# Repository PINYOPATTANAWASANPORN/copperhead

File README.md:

<p align="center">
  
</p>

<p align="center">

</p>

**Cursor for circuit boards.** An AI agent that designs, documents, and validates real PCBs from a prompt, working directly on existing KiCad repositories.

> **Status: early.** Phase 1 is implemented and the CLI runs. The [technical specification](openspec/specs/SPEC.md) is the source of truth; expect the surface to move before 1.0.

Full documentation lives at [docs.copperhead.sh](https://docs.copperhead.sh).

## What it is

An AI product-development agent for hardware: from a product brief to manufacturable files, firmware, and a build plan.

- **`copperhead create`**: full pipeline from a natural-language brief: spec, architecture, part selection, schematic, first-draft layout, then gerbers, firmware scaffold, and dev plan.
- **`copperhead do "<change>"`**: operates on an existing KiCad repo the way a coding agent operates on a codebase.

It reads and edits real `.kicad_sch` / `.kicad_pcb` files (s-expression text), maintains markdown design docs as memory, propagates every change across all artifacts that reference it, and verifies its own work by running `kicad-cli` ERC/DRC until the checks pass.

## Install

> [!TIP]
> **Most users should not install copperhead by hand.** If you are working inside an AI coding assistant (like Claude Code, Cursor, or Codex), you can install and configure copperhead automatically for your repository by pasting this single line:
> ```text
> Install copperhead for this repo using https://raw.githubusercontent.com/copperheadhq/copperhead/main/agent-install-prompt.md
> ```

If you prefer to install manually:

```bash
npm install -g copperhead   # or: npx copperhead check
```

### Bootstrap script (macOS and Linux)

Prefer a one-command setup? [`install.sh`](install.sh) checks the prerequisites below, installs copperhead (globally via npm, or built from source when run inside a checkout), and verifies the result with `copperhead doctor`:

```bash
./install.sh                # interactive: asks before installing anything
./install.sh --yes          # assume yes to the install prompts
./install.sh --check-only   # report what is missing, install nothing
```

The script is conservative by design: it never runs `sudo` and never edits shell config; whenever it cannot act safely on its own it prints the exact command for you to run instead. Rerunning is safe: on a ready machine it installs nothing and exits 0.

### Requirements

- Node.js ≥ 20
- [KiCad](https://www.kicad.org/) ≥ 8 with `kicad-cli` on PATH (on Windows and macOS, copperhead also searches standard installation directories automatically; override with `COPPERHEAD_KICAD_CLI`)
- One model backend: a locally installed, ChatGPT-authenticated [Codex CLI](https://learn.chatgpt.com/docs/codex/cli), a logged-in [Cursor Agent CLI](#saved-login-cursor-agent) (`agent login`), logged-in Claude Code (see [Saved login](#saved-login-claude-code)), or `ANTHROPIC_API_KEY`/`OPENAI_API_KEY` in the environment. `check` never calls an LLM.

## Quick start

In an existing KiCad repository:

```bash
export ANTHROPIC_API_KEY=...   # or OPENAI_API_KEY; optional: with no key, `copperhead` offers a model picker
copperhead init                # scaffold docs/ from the schematic; idempotent
copperhead                     # interactive agent shell (Claude Code–style REPL)
copperhead demo --tour          # what the agent does (no LLM)
copperhead demo --model cursor # full USB-C breakout create pipeline
# or one-shot:
copperhead do "add reverse-polarity protection on VIN"
copperhead check               # ERC + DRC + doc drift; no LLM, CI-safe
```

Starting from nothing instead? Write a product brief and run `copperhead create --brief brief.md`. The [examples/](examples/) directory has ready-made briefs sorted by difficulty, plus a note on which one is designed to fail.

### Use your existing Codex login

No model API key is needed when Codex CLI is already authenticated:

```bash
npm install -g @openai/codex-sdk   # optional adapter, loaded only for --model codex
codex login status
copperhead do "rename net KEY_DAH to KEY_DASH" --model codex
```

Plain `codex` follows your Codex model configuration. Use `codex:<model-id>` for an explicit model. If the executable is not on `PATH`, set `COPPERHEAD_CODEX_PATH=/absolute/path/to/codex`.
The optional SDK also installs a compatible launcher; for a global install, use
`COPPERHEAD_CODEX_PATH="$(npm root -g)/@openai/codex/bin/codex.js"` as a fallback.

Codex's read-only sandbox prevents native writes but does not confine native reads. Copperhead instructs Codex not to use its own filesystem tools, but the CLI can technically read files such as `.env`. Codex also keeps session logs under `~/.codex/sessions/`; those files are outside Copperhead's transcript-redaction boundary and should be protected according to your local data-retention policy.

## How it works

It's a loop, and it looks a lot like pair-programming, except the codebase is a circuit board.

1. **Start from the docs.** Every decision lives in the design docs, so the agent reads those first and knows the whole design, not just the part in front of it.
2. **Talk through the change.** Describe what you want ("add an external key jack", "cut the sleep current"). The agent proposes the parts and circuit; you push back until the reasoning holds up.
3. **Edit the real files.** The agent writes changes straight into the KiCad schematic and the design docs, using the same part names and net names everywhere so nothing drifts.
4. **Propagate.** Change one value, like a charge current or a pin, and it carries across every doc and schematic that references it. The boring, easy-to-get-wrong step is the one the agent is best at.
5. **Check the work.** The agent runs ERC/DRC, reads the errors back, and fixes them. Nothing is "done" until the tools agree.
6. **Write down why.** Every real decision gets a one-line reason next to it, so the next change doesn't quietly undo it.

Two invariants make this trustworthy:

1. **Nothing starts without a spec.** The agent cannot touch a KiCad file until a validated change proposal exists; the edit tools are structurally unavailable until it does. Every edit is traceable to a documented intent.
2. **Nothing is "done" until the tools agree.** Every file mutation is followed by an ERC/DRC run before the agent reports success.

Spec-gated in, verification-gated out: the design can't drift from its requirements, because drift is a build failure.

## CLI

```text
copperhead init [--path hardware/]   # scaffold docs/ from an existing schematic; idempotent
copperhead do "<change request>"     # the core loop: propose, edit, verify, propagate, commit
copperhead check                     # ERC + DRC + doc-drift + spec validation; no LLM calls (alias: verify)
copperhead doctor                    # env preflight: node, kicad-cli, git, openspec, provider credential; no LLM/network
copperhead sync [--dry-run]          # verify the whole design state, resolve drift
copperhead create --brief brief.md   # brief → full output package
copperhead export bom --supplier jlcpcb   # supplier-ready ordering file from docs/BOM.md
copperhead pcb route --mode staged   # layout harness: wrapped routers, independent verification, ranked candidates (RFC 11)
copperhead pcb verify | render       # harness checkers on one board; SVG with the diagnostics marked
```

Global flags: `--repo <path>` (default: cwd) and `--json` for machine-readable output. `--model` is available on `do`, `sync`, `create`, and `doctor`; `--interactive` only on `do` and `create`; `do` also takes `--dry-run`, `--max-turns`, and `--allow-dirty`.

`--model` accepts `gpt-5` (OpenAI), `claude` / `claude-<id>` (Anthropic API), `claude-code` / `claude-code:<id>` (Claude Code, saved login), `cursor` / `cursor:<id>` (Cursor Agent CLI, saved login), and `codex` / `codex:<id>` (Codex CLI, saved login). Routing is by prefix; `claude-code` is matched before the `claude` prefix. `compat:<id>` targets any OpenAI-compatible endpoint (Groq, OpenRouter, Gemini, or a local Ollama) via `COPPERHEAD_BASE_URL` and `COPPERHEAD_API_KEY_ENV` - worked examples for each in [`.env.example`](.env.example) and the [configuration reference](https://docs.copperhead.sh/reference/configuration/#model-selection).

### Saved login (Cursor Agent)

`--model cursor` drives the Cursor Agent CLI with your saved login from `agent login`, so you can run copperhead with **no `OPENAI_API_KEY` or `ANTHROPIC_API_KEY`**. Cursor is used purely as a reasoning backend in plan mode: the agent loop, safety gates, and every file edit stay inside copperhead.

```bash
agent status
copperhead do "add reverse-polarity protection on VIN" --model cursor
```

If `agent` is not on `PATH`, set `COPPERHEAD_CURSOR_PATH` to the CLI binary (also available as `cursor-agent` on some installs). Cursor's JSON schema does not report token usage, so run summaries show 0 tokens for `--model cursor`.

### Saved login (Claude Code)

`--model claude-code` drives Claude Code through the [Claude Agent SDK](https://code.claude.com/docs/en/agent-sdk) and reuses your saved login (the `CLAUDE_CODE_OAUTH_TOKEN` from `claude setup-token`), so a Claude subscription runs copperhead with **no `ANTHROPIC_API_KEY`**. Claude Code is used purely as a reasoning backend: the agent loop, its safety gates, and every file edit stay inside copperhead, identical to the other providers.

```bash
claude setup-token                          # while logged into Claude Code
export CLAUDE_CODE_OAUTH_TOKEN=...           # the token setup-token printed
copperhead do "add reverse-polarity protection on VIN" --model claude-code
```

The Claude Agent SDK ships as an optional dependency, so a normal install pulls it in. copperhead loads it only when you select `claude-code`, and prints an actionable error if it is missing (for example after `npm install --omit=optional`), telling you to add it with `npm i @anthropic-ai/claude-agent-sdk`.

copperhead never reads, copies, or logs the credential; the CLI owns authentication. A missing dependency or an unauthenticated install fails with an actionable message and touches nothing.

### Ordering (`export bom`)

`copperhead export bom` turns the drift-checked `docs/BOM.md` into a file a supplier accepts without hand-editing. It is deterministic, LLM-free, and network-free, safe anywhere `check` is, and it reads `BOM.md` (never the schematic) so it inherits the drift guarantee; it refuses to export while `BOM.md` disagrees with the schematic.

```bash
copperhead export bom --supplier jlcpcb                 # JLCPCB assembly CSV → outputs/jlcpcb-bom.csv
copperhead export bom --supplier digikey --boards 25    # DigiKey cart CSV, quantities for 25 boards
copperhead export bom --supplier mouser --spares 15     # Mouser cart CSV, 15% spare parts
```

- `--supplier <jlcpcb|digikey|mouser>` (required). JLCPCB gets the assembly-service format (Comment, Designator, Footprint, LCSC Part #, designators grouped per line); DigiKey and Mouser get cart-upload lists (MPN, manufacturer, quantity, customer reference).
- `--boards <n>` (default 1) and `--spares <percent>` (default 10) set the order quantity: `ceil(perBoardCount × boards × (1 + spares/100))`, raised to `perBoardCount × boards + 2` for passive lines (footprints `R_`/`C_`/`L_`); losing a couple of 0402s to tweezers is the norm, and percentage-only spares under-order low-count passives.
- Rows without an MPN, and rows still flagged `UNVERIFIED`, are excluded from the supplier file and named in a warnings footer on stderr. `--include-unverified` opts the flagged-but-MPN'd rows back in (it never includes MPN-less rows). `create` stage 6 also emits `outputs/jlcpcb-bom.csv` automatically.

`docs/BOM.md` may carry optional `Manufacturer` and `LCSC` columns beyond the base `Refdes | Value | Footprint | MPN | Rationale`; the exporter matches columns by header, so add them when you want them populated in supplier files; `init` scaffolds the base columns only. Only *appending* columns is safe: keep `Refdes | Value | Footprint` first and in that order, because the drift check (`check`/`sync`, which the exporter gates on) reads those three by position, so reordering them makes it compare the wrong cells and refuse the export with a spurious drift message.

Nothing is a black box: decisions land in an append-only `docs/DECISIONS.md`, every run writes a human-readable summary next to its transcript, and a per-run `docs/CHANGELOG.md` narrates the design history.

### Board layout

copperhead lays boards out the same way it does everything else: it never places or routes a board itself. It wraps engines that do (Freerouting, kicad-tools, pyplacer) behind one fail-closed contract and owns everything around them: the board representation, the intent you declare in YAML (edges, attachments, groups, keepouts, widths), the rule stages that satisfy that intent before any engine runs, the verification every candidate must pass (its own geometry and connectivity checks, with KiCad DRC as one voter), the ranking, the repair loop, and the evidence written into `docs/LAYOUT.md`. `copperhead check` re-verifies a laid-out board from then on. The supported envelope is two layers, low-speed digital and DC power, under 50 parts; anything else ends in `HOLD` or `REFUSE` with the reason. Details: [the layout framework](docs/src/content/docs/concepts/layout-framework.md), [RFC 11](https://github.com/copperheadhq/copperhead-rfcs/blob/main/rfc/rfc11.md), and the milestone reports under [`bench/reports/`](https://github.com/copperheadhq/copperbench/tree/main/bench/reports) in [copperbench](https://github.com/copperheadhq/copperbench), which measures the engines and the placers.

## What it is not

- **Not an autorouter or a placer.** copperhead wraps existing engines and verifies their output; it does not build its own, and every result is measured against the human baseline before anything is claimed.
- **Not a new editor.** No walled garden; your KiCad install remains the editor.
- **Not the engineer of record.** A human signs off; the agent never claims a design is fab-ready beyond "ERC/DRC clean".

## Simple demo

From a checkout of this repo, run the smallest create-pipeline demo with the USB-C power breakout brief:

```bash
npm run demo:simple
```

The script creates or resumes a git repo at `demo-runs/usb-c-breakout/` and runs:

```bash
copperhead create --brief examples/simple/usb-c-breakout.md
```

Pass normal create flags after `--`, for example `npm run demo:simple -- --model claude`.
If a stage fails, rerun the same command; the demo repo keeps a baseline commit and ignores run transcripts so retries start from the last committed design state.

More briefs, including medium and hard tiers, live in [examples/](examples/).

## Maturity

Honest read of where the current release stands, so you can calibrate before pointing this at a board you care about:

- **Solid.** `init` and `check`/`verify` are deterministic, LLM-free, and covered by the offline test suite against a real KiCad fixture: scaffolding, ERC/DRC, the s-expression reader, drift detection, and fab export all run green in CI.
- **Implemented, not yet proven.** The agent loop (`do`, `sync --resolve`, `create`) is complete and structurally gated, but its acceptance tests need a live model and have not been observed passing end to end. Expect rough edges.
- **Always.** Every mutation runs inside a git snapshot and rolls back if verification fails, so the worst case is a no-op commit, not a mangled schematic. Work on a branch anyway.

## Open source

The entire tool (agent core, prompts, tools) is public under Apache-2.0, built on an open stack (KiCad, kicad-cli, [OpenSpec](https://github.com/Fission-AI/OpenSpec)). Everything it produces is plain markdown and JSON in your own repo: no proprietary formats, no lock-in. This is a Chouhan Industries project, and the same commitment that puts every hardware schematic in public applies to the tool that designs them.

## Contributing

Contributions are welcome; see [CONTRIBUTING.md](CONTRIBUTING.md) for setup and workflow. Note that your first pull request requires signing the [Contributor License Agreement](.github/cla/CLA.md); a bot posts instructions on the PR and signing is a one-time comment.

## Project layout

- [`AGENTS.md`](AGENTS.md): repository instructions loaded automatically by Codex and compatible coding agents; [`CLAUDE.md`](CLAUDE.md) provides the corresponding Claude Code guidance
- [`src/`](src/): CLI ([`cli.ts`](src/cli.ts), [`commands/`](src/commands/)), the provider-agnostic agent loop ([`agent/`](src/agent/)), the `kicad-cli` wrapper and s-expression reader ([`kicad/`](src/kicad/)), and doc/constraint memory ([`memory/`](src/memory/))
- [`test/`](test/): offline suite plus [`fixtures/`](test/fixtures/), a tiny known-good KiCad project
- [`openspec/specs/SPEC.md`](openspec/specs/SPEC.md): the full technical specification, including binary acceptance criteria
- [`openspec/changes/build-copperhead-phase-1/`](openspec/changes/build-copperhead-phase-1/): the implementation plan with proposal, design decisions, capability specs, and task checklist

## License

[Apache-2.0](LICENSE)

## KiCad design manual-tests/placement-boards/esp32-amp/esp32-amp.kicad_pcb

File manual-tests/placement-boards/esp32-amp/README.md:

# esp32-amp

An ESP32-S3 I2S class-D amplifier board, built as a placement subject. See [../README.md](../README.md) for how placement boards work and how to run one.

## The design

USB-C in, mono speaker out, five subsystems in signal-flow order:

| Subsystem | Parts | What it has to satisfy |
| --- | --- | --- |
| Power Input | J1, R1, R2, F1, D1, CP1 | receptacle on a board edge; CC pulldowns and the TVS at the receptacle; bulk cap feeding the class-D stage |
| Regulation | U2, C1, C2, R3, D2 | AP2112K-3.3 with its input and output caps at their own pins |
| MCU | U1, C3, C4, R4, C5, SW1, SW2, J3 | ESP32-S3-WROOM-1 decoupled at pad 2; EN network and buttons reachable; UART header on an edge |
| Amplifier | U3, C6, C7, R5, R6, R7 | MAX98357A on the 5V rail, decoupled at both VDD pads; select resistors at their high-impedance pins |
| Speaker Output | FB1, FB2, C8, C9, J2 | bridged output through an EMI filter into a terminal on the opposite edge from USB-C |

30 parts, 22 declared nets (57 after KiCad names the unconnected pins), 68 × 64 mm two-layer outline. The schematic passes ERC with 0 errors and 1 warning (the MAX98357A thermal pad is an Unspecified-type pin tied to GND — correct, and not suppressible from the intent IR).

`layout-intent.yaml` states the requirements above in the RFC 11 §7.3 intent language: three edge-fixed connectors, 18 attachments, two groups. It is **not** applied by default — see the generations below for why that matters.

## Regenerating the inputs

The committed schematic and grid board came from:

```bash
# 1. bootstrapKicadProject() scaffolds the empty project and wires config
# 2. draft the sheet from schematic.intent.json
copperhead --repo manual-tests/placement-boards/esp32-amp draft schematic
# 3. populateBoard() puts a resolved footprint for every part on a shelf-pack grid
```

Steps 1 and 3 have no CLI surface yet (they live inside `create`'s pipeline), so they were driven directly through `src/kicad/bootstrap.ts` and `src/kicad/board.ts`. Both are deterministic given the same installed KiCad libraries.

## Generations

One directory per build under `generations/`. Each holds `placed.kicad_pcb`, `before.png`/`after.png`, `ranking.json`, `place.log` and a summary table.

| Generation | Outcome | Selected | HPWL | Connector nearest its edge | What changed |
| --- | --- | --- | --- | --- | --- |
| `2026-09-16-9597b5f` | PASS | placer-reuse-pack | 596.3 mm | 2.68 mm (J1, west) | the first baseline |
| `2026-09-16-9597b5f-intent` | PARTIAL | none | — | 0.75 mm (edges honoured) | `layout-intent.yaml` applied; every candidate fails on `placer-attach` stacking same-pin siblings |
| `2026-09-16-connector-edges` | PASS | placer-reuse-pack | 635.7 mm | 0.75 mm (all three) | connector edges derived from block regions (ADR 0013) |

The wirelength went up between the first and third generations and that is the improvement: the first board was shorter because it packed the USB-C receptacle into the middle, where no plug reaches it.

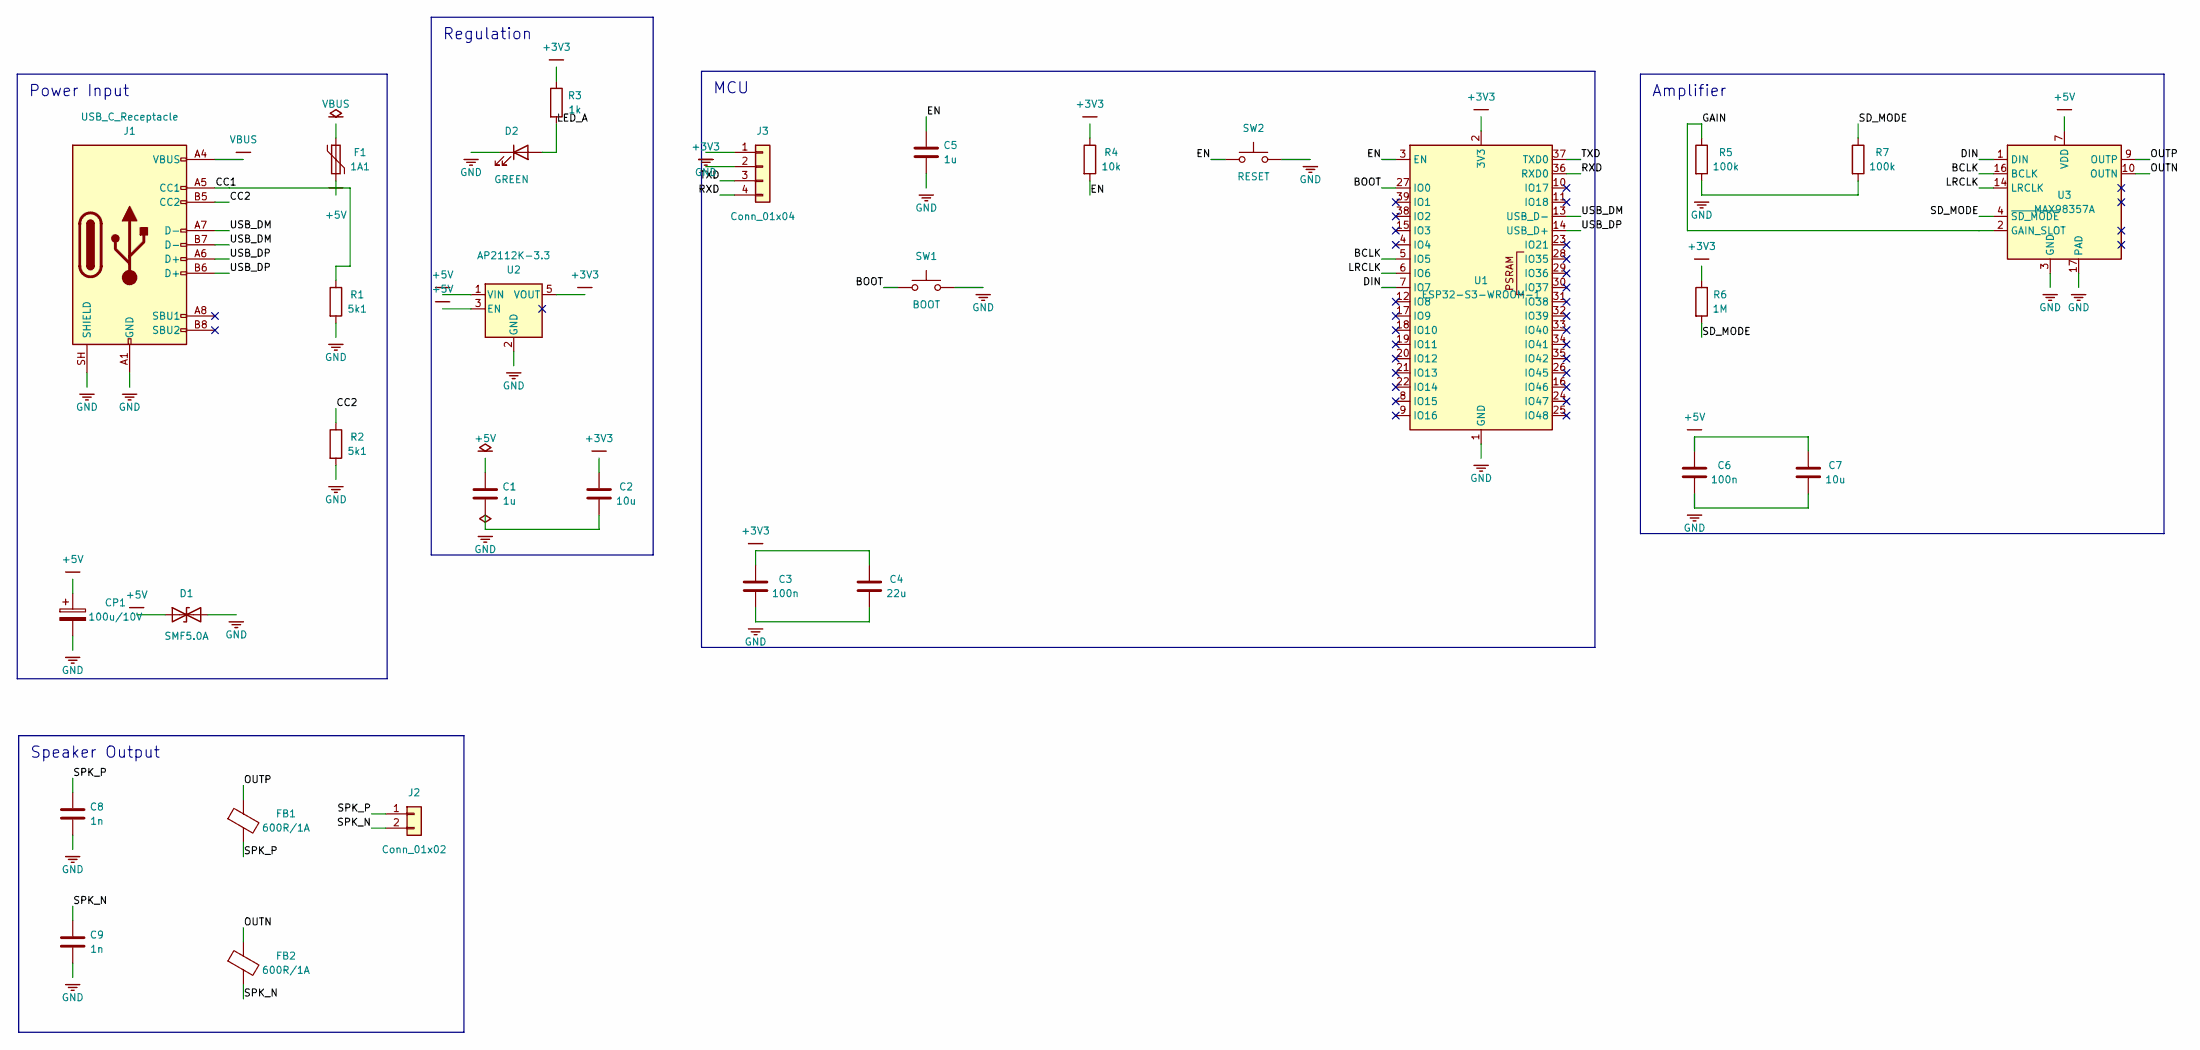
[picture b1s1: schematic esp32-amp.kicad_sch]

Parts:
C1: 1u; C_0603_1608Metric
C2, C7: 10u; C_0805_2012Metric
C3, C6: 100n; C_0402_1005Metric
C4: 22u; C_0805_2012Metric
C5: 1u; C_0402_1005Metric
C8, C9: 1n; C_0402_1005Metric
CP1: 100u/10V; CP_Elec_6.3x7.7
D1: SMF5.0A; D_SOD-123
D2: GREEN; LED_0603_1608Metric
F1: 1A1; Fuse_1812_4532Metric
FB1, FB2: 600R/1A; L_0805_2012Metric
J1: USB_C_Receptacle; USB_C_Receptacle_HCTL_HC-TYPE-C-16P-01A
J2: Conn_01x02; TerminalBlock_Phoenix_MPT-0,5-2-2.54_1x02_P2.54mm_Horizontal
J3: Conn_01x04; PinHeader_1x04_P2.54mm_Vertical
R1, R2: 5k1; R_0402_1005Metric
R3: 1k; R_0603_1608Metric
R4: 10k; R_0402_1005Metric
R5, R7: 100k; R_0402_1005Metric
R6: 1M; R_0402_1005Metric
SW1: BOOT; SW_Push_1P1T_NO_CK_KMR2
SW2: RESET; SW_Push_1P1T_NO_CK_KMR2
U1: ESP32-S3-WROOM-1
U2: AP2112K-3.3; SOT-23-5
U3: MAX98357A; TQFN-16-1EP_3x3mm_P0.5mm_EP1.23x1.23mm

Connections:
+3V3: C2.1, C3.1, C4.1, J3.2, R3.1, R4.1, R6.1, U1.2 (3V3), U2.5 (VOUT)
+5V: C1.1, C6.1, C7.1, CP1.1, D1.1 (A1), F1.2, U2.1 (VIN), U2.3 (EN), U3.7 (VDD), U3.8 (VDD)
/BCLK: U1.5 (IO5), U3.16 (BCLK)
/BOOT: SW1.1, U1.27 (IO0)
/CC1: J1.A5 (CC1), R1.1
/CC2: J1.B5 (CC2), R2.1
/DIN: U1.7 (IO7), U3.1 (DIN)
/EN: C5.1, R4.2, SW2.1, U1.3 (EN)
/GAIN: R5.1, U3.2 (GAIN_SLOT)
/LED_A: D2.2 (A), R3.2
/LRCLK: U1.6 (IO6), U3.14 (LRCLK)
/OUTN: FB2.1, U3.10 (OUTN)
/OUTP: FB1.1, U3.9 (OUTP)
/RXD: J3.4, U1.36 (RXD0)
/SD_MODE: R6.2, R7.1, U3.4 (~SD_MODE)
/SPK_N: C9.1, FB2.2, J2.2
/SPK_P: C8.1, FB1.2, J2.1
/TXD: J3.3, U1.37 (TXD0)
/USB_DM: J1.A7 (D-), J1.B7 (D-), U1.13 (USB_D-)
/USB_DP: J1.A6 (D+), J1.B6 (D+), U1.14 (USB_D+)
GND: C1.2, C2.2, C3.2, C4.2, C5.2, C6.2, C7.2, C8.2, C9.2, CP1.2, D1.2 (A2), D2.1 (K), J1.A1 (GND), J1.A12 (GND), J1.B1 (GND), J1.B12 (GND), J1.SH (SHIELD), J3.1, R1.2, R2.2, R5.2, R7.2, SW1.2, SW2.2, U1.1 (GND), U1.40 (GND), U1.41 (GND), U2.2 (GND), U3.3 (GND), U3.11 (GND), U3.15 (GND), U3.17 (PAD)
VBUS: F1.1, J1.A4 (VBUS), J1.A9 (VBUS), J1.B4 (VBUS), J1.B9 (VBUS)

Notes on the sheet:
Amplifier
MCU
Power Input
Regulation
Speaker Output

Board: 2 copper layers, 30 parts (0 on the bottom side), 22 nets, no tracks yet.

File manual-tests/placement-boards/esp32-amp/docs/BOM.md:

# BOM

| Refdes | Value | Footprint | MPN | Rationale |
| --- | --- | --- | --- | --- |
| J1 | USB_C_Receptacle | Connector_USB:USB_C_Receptacle_HCTL_HC-TYPE-C-16P-01A | UNVERIFIED | 5V input, USB 2.0 data to the module |
| R1 | 5k1 | Resistor_SMD:R_0402_1005Metric | UNVERIFIED | CC1 pulldown, advertises a sink |
| R2 | 5k1 | Resistor_SMD:R_0402_1005Metric | UNVERIFIED | CC2 pulldown, advertises a sink |
| F1 | 1A1 | Fuse:Fuse_1812_4532Metric | UNVERIFIED | resettable fuse on VBUS |
| D1 | SMF5.0A | Diode_SMD:D_SOD-123 | UNVERIFIED | bidirectional TVS on the 5V rail |
| CP1 | 100u/10V | Capacitor_SMD:CP_Elec_6.3x7.7 | UNVERIFIED | bulk reservoir for the class-D output stage |
| U2 | AP2112K-3.3 | Package_TO_SOT_SMD:SOT-23-5 | UNVERIFIED | 600 mA 3V3 LDO for the module |
| C1 | 1u | Capacitor_SMD:C_0603_1608Metric | UNVERIFIED | LDO input capacitor |
| C2 | 10u | Capacitor_SMD:C_0805_2012Metric | UNVERIFIED | LDO output capacitor |
| R3 | 1k | Resistor_SMD:R_0603_1608Metric | UNVERIFIED | rail LED series resistor |
| D2 | GREEN | LED_SMD:LED_0603_1608Metric | UNVERIFIED | 3V3 rail indicator |
| U1 | ESP32-S3-WROOM-1 | RF_Module:ESP32-S3-WROOM-1 | UNVERIFIED | Wi-Fi SoC module, I2S master |
| C3 | 100n | Capacitor_SMD:C_0402_1005Metric | UNVERIFIED | module decoupling |
| C4 | 22u | Capacitor_SMD:C_0805_2012Metric | UNVERIFIED | module bulk decoupling for Wi-Fi bursts |
| R4 | 10k | Resistor_SMD:R_0402_1005Metric | UNVERIFIED | EN pullup |
| C5 | 1u | Capacitor_SMD:C_0402_1005Metric | UNVERIFIED | EN power-on delay |
| SW1 | BOOT | Button_Switch_SMD:SW_Push_1P1T_NO_CK_KMR2 | UNVERIFIED | pulls IO0 low for download mode |
| SW2 | RESET | Button_Switch_SMD:SW_Push_1P1T_NO_CK_KMR2 | UNVERIFIED | pulls EN low |
| J3 | Conn_01x04 | Connector_PinHeader_2.54mm:PinHeader_1x04_P2.54mm_Vertical | UNVERIFIED | UART0 programming header |
| U3 | MAX98357A | Package_DFN_QFN:TQFN-16-1EP_3x3mm_P0.5mm_EP1.23x1.23mm | UNVERIFIED | 3.2W I2S class-D amplifier |
| C6 | 100n | Capacitor_SMD:C_0402_1005Metric | UNVERIFIED | amplifier decoupling |
| C7 | 10u | Capacitor_SMD:C_0805_2012Metric | UNVERIFIED | amplifier bulk decoupling |
| R5 | 100k | Resistor_SMD:R_0402_1005Metric | UNVERIFIED | GAIN_SLOT to GND, 12 dB gain |
| R6 | 1M | Resistor_SMD:R_0402_1005Metric | UNVERIFIED | SD_MODE divider upper leg |
| R7 | 100k | Resistor_SMD:R_0402_1005Metric | UNVERIFIED | SD_MODE divider lower leg, selects left channel |
| FB1 | 600R/1A | Inductor_SMD:L_0805_2012Metric | UNVERIFIED | EMI filter on OUTP |
| FB2 | 600R/1A | Inductor_SMD:L_0805_2012Metric | UNVERIFIED | EMI filter on OUTN |
| C8 | 1n | Capacitor_SMD:C_0402_1005Metric | UNVERIFIED | output filter cap on SPK_P |
| C9 | 1n | Capacitor_SMD:C_0402_1005Metric | UNVERIFIED | output filter cap on SPK_N |
| J2 | Conn_01x02 | TerminalBlock_Phoenix:TerminalBlock_Phoenix_MPT-0,5-2-2.54_1x02_P2.54mm_Horizontal | UNVERIFIED | speaker terminal |

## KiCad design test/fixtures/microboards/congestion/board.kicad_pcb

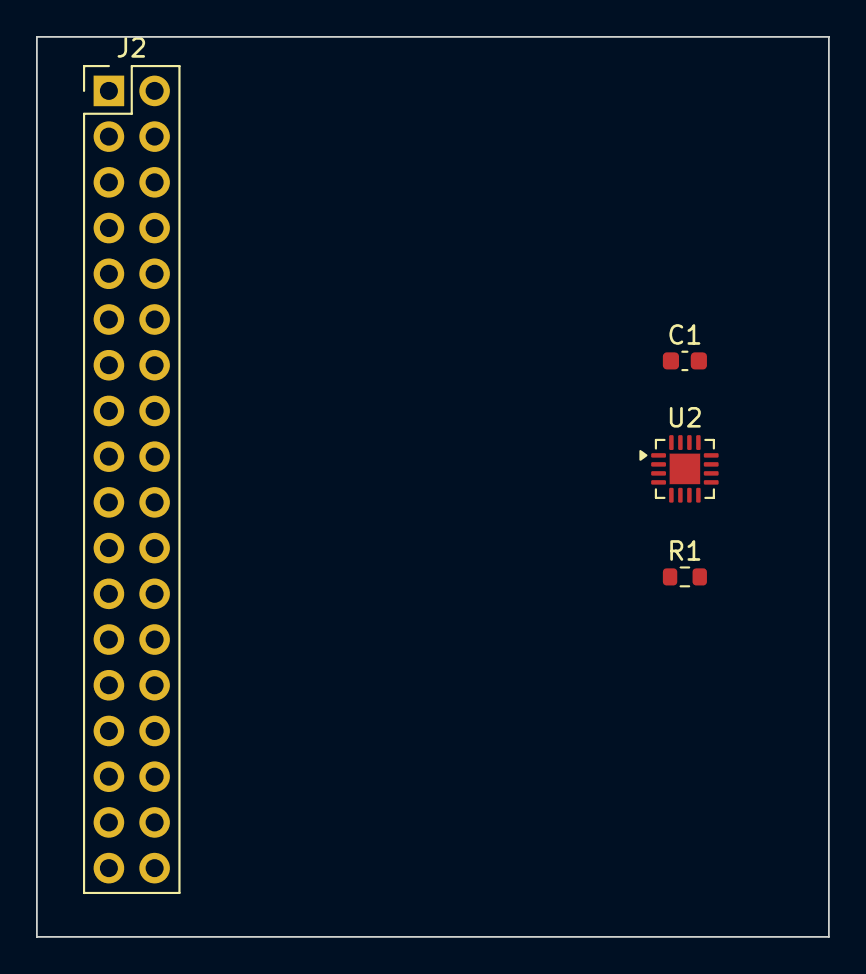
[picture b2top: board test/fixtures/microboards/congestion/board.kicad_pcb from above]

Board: 2 copper layers, 44.0 x 50.0 mm, 4 parts (0 on the bottom side), 19 nets, no tracks yet.

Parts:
C1: 100n; C_0603_1608Metric
J2: CONN; PinHeader_2x18_P2.54mm_Vertical
R1: 10k; R_0603_1608Metric
U2: MCU; QFN-16-1EP_3x3mm_P0.5mm_EP1.7x1.7mm

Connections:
GND: C1.2, J2.36, U2.17
PU: J2.34, R1.2
S1: J2.1, U2.1
S2: J2.2, U2.2
S3: J2.3, U2.3
S4: J2.4, U2.4
S5: J2.5, U2.5
S6: J2.6, U2.6
S7: J2.7, U2.7
S8: J2.8, U2.8
S9: J2.9, U2.9
S10: J2.10, U2.10
S11: J2.11, U2.11
S12: J2.12, U2.12
S13: J2.13, U2.13
S14: J2.14, U2.14
S15: J2.15, U2.15
S16: J2.16, U2.16
VCC: C1.1, J2.35, R1.1

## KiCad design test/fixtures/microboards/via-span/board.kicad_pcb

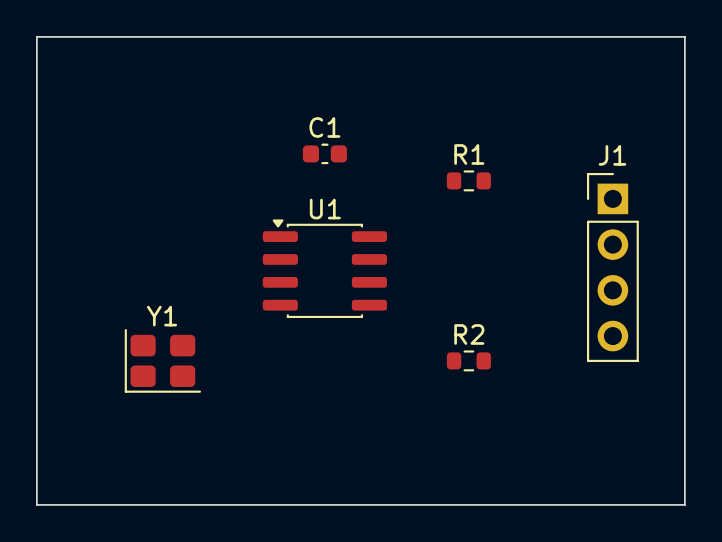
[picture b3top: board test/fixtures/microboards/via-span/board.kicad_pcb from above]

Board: 4 copper layers, 36.0 x 26.0 mm, 6 parts (0 on the bottom side), 6 nets.

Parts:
C1: 100n; C_0603_1608Metric
J1: CONN; PinHeader_1x04_P2.54mm_Vertical
R1, R2: 10k; R_0603_1608Metric
U1: MCU; SOIC-8_3.9x4.9mm_P1.27mm
Y1: 8MHz; Crystal_SMD_3225-4Pin_3.2x2.5mm

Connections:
GND: C1.2, J1.2, U1.4, Y1.2, Y1.4
SIG1: J1.3, R1.2, U1.1
SIG2: J1.4, R2.2, U1.2
VCC: C1.1, J1.1, R1.1, R2.1, U1.8
XI: U1.5, Y1.1
XO: U1.6, Y1.3

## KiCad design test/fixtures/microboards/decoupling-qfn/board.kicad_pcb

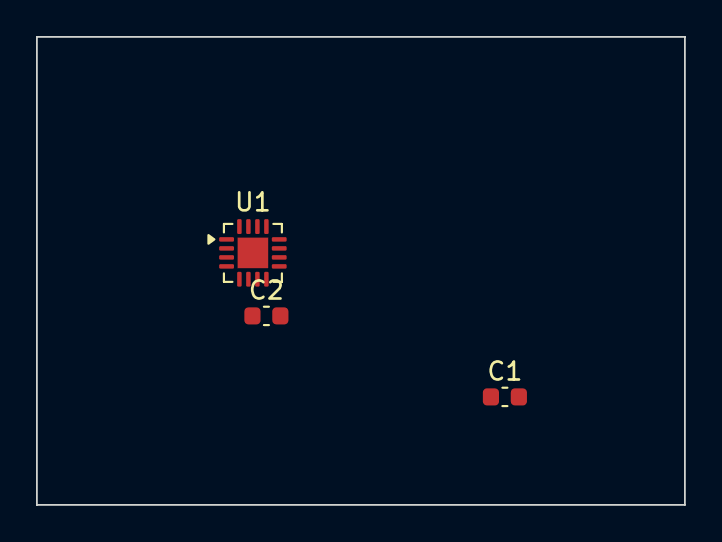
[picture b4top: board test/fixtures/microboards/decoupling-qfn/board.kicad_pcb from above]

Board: 2 copper layers, 36.0 x 26.0 mm, 3 parts (0 on the bottom side), 3 nets, no tracks yet.

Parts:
C1, C2: 100n; C_0603_1608Metric
U1: RF; QFN-16-1EP_3x3mm_P0.5mm_EP1.7x1.7mm

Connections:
GND: C1.2, C2.2, U1.17
VDD: C1.1, U1.16
VDDA: C2.1, U1.8

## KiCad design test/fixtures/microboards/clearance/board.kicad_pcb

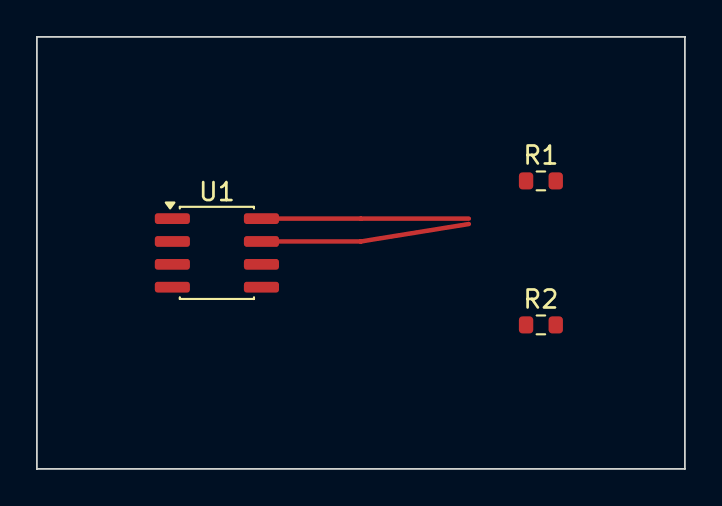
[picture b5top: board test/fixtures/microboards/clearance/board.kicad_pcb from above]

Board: 2 copper layers, 36.0 x 24.0 mm, 3 parts (0 on the bottom side), 3 nets.

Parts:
R1, R2: 10k; R_0603_1608Metric
U1: MCU; SOIC-8_3.9x4.9mm_P1.27mm

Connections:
GND: R1.2, R2.2, U1.4
SIG1: R1.1, U1.8
SIG2: R2.1, U1.7

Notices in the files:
test/fixtures/microboards/clearance/board.kicad_pcb:
copperhead golden microboard; footprints from the KiCad libraries (CC-BY-SA-4.0 with the KiCad library exception)
